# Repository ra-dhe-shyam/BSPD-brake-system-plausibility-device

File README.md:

"# BSPD-brake-system-plausibility-device" 
#BSPD-brake-system-plausibility-device-

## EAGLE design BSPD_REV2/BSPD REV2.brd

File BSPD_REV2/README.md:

Revision 2 of BSPD schematic and layout.

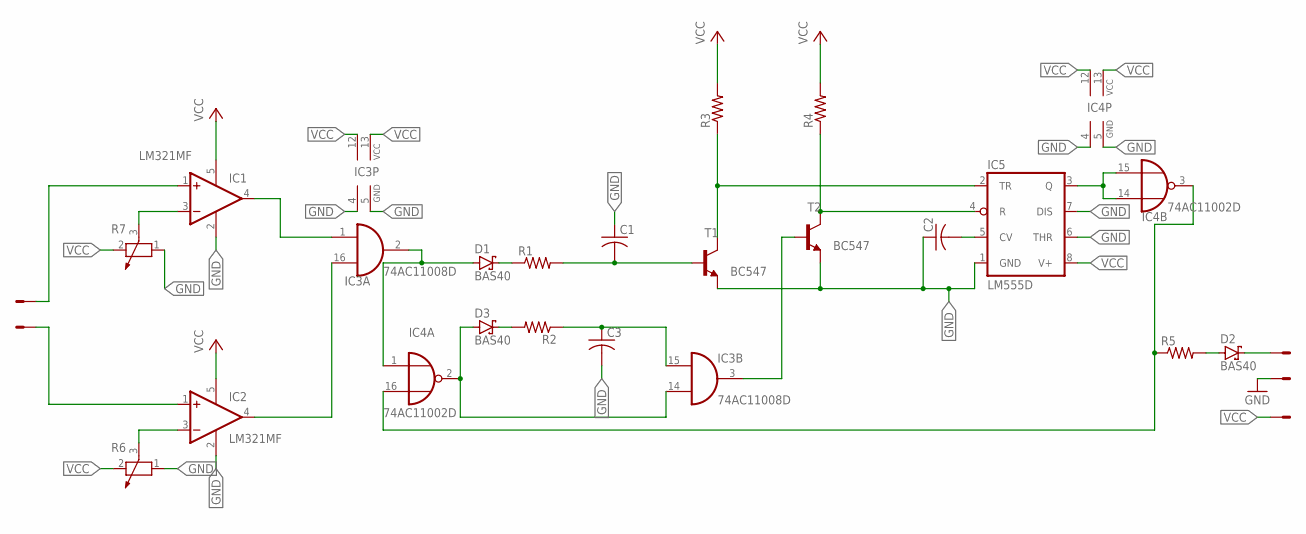
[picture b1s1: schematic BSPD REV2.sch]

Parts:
C1, C2, C3: C-USC0402; C0402
D1, D2, D3: BAS40; SOT23
IC1, IC2: LM321MF; SOT23-5
IC3: 74AC11008D; SO16
IC4: 74AC11002D; SO16
IC5: LM555D; SO08
R1, R2, R3, R4, R5: R-US_M1406; M1406
R6, R7: POTENTIOMETER_PT_SPIN; PT-SPIN
T1, T2: BC547; TO92
X1: 22-23-2051

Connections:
GND: C1.1, C2.1, C3.2, IC1.2 (V-), IC2.2 (V-), IC3.4 (GND), IC3.5 (GND), IC4.4 (GND), IC4.5 (GND), IC5.1 (GND), IC5.6 (THR), IC5.7 (DIS), R6.1, R7.1, T1.1 (E), T2.1 (E), X1.2
unnamed: IC1.1 (+IN), X1.3
unnamed: IC2.1 (+IN), X1.4
unnamed: IC1.3 (-IN), R7.3
unnamed: IC2.3 (-IN), R6.3
unnamed: IC1.4 (OUT), IC3.1 (I0)
unnamed: IC2.4 (OUT), IC3.16 (I1)
unnamed: D1.1 (A), IC3.2 (O), IC4.1 (I0)
unnamed: IC4.3 (O), IC4.16 (I1), R5.1
unnamed: D1.3 (C), R1.1
unnamed: D3.1 (A), IC3.14 (I1), IC4.2 (O)
unnamed: D3.3 (C), R2.2
unnamed: C3.1, IC3.15 (I0), R2.1
unnamed: C1.2, R1.2, T1.2 (B)
unnamed: IC5.2 (TR), R3.1, T1.3 (C)
unnamed: IC5.4 (R), R4.1, T2.3 (C)
unnamed: D2.1 (A), R5.2
unnamed: IC3.3 (O), T2.2 (B)
unnamed: C2.2, IC5.5 (CV)
unnamed: IC4.14 (I1), IC4.15 (I0), IC5.3 (Q)
unnamed: D2.3 (C), X1.1
VCC: IC1.5 (V+), IC2.5 (V+), IC3.12 (VCC), IC3.13 (VCC), IC4.12 (VCC), IC4.13 (VCC), IC5.8 (V+), R3.2, R4.2, R6.2, R7.2, X1.5

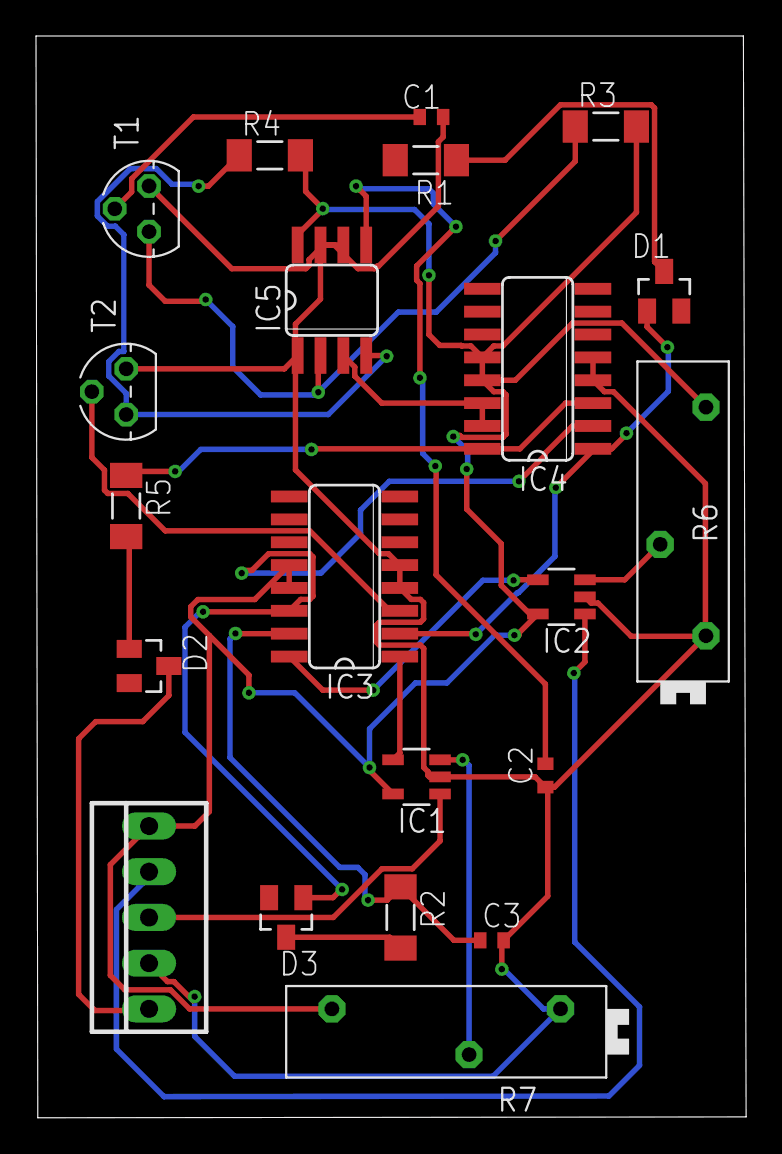
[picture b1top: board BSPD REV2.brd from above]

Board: 2 copper layers, 39.4 x 60.1 mm, 21 parts (0 on the bottom side), 22 nets.

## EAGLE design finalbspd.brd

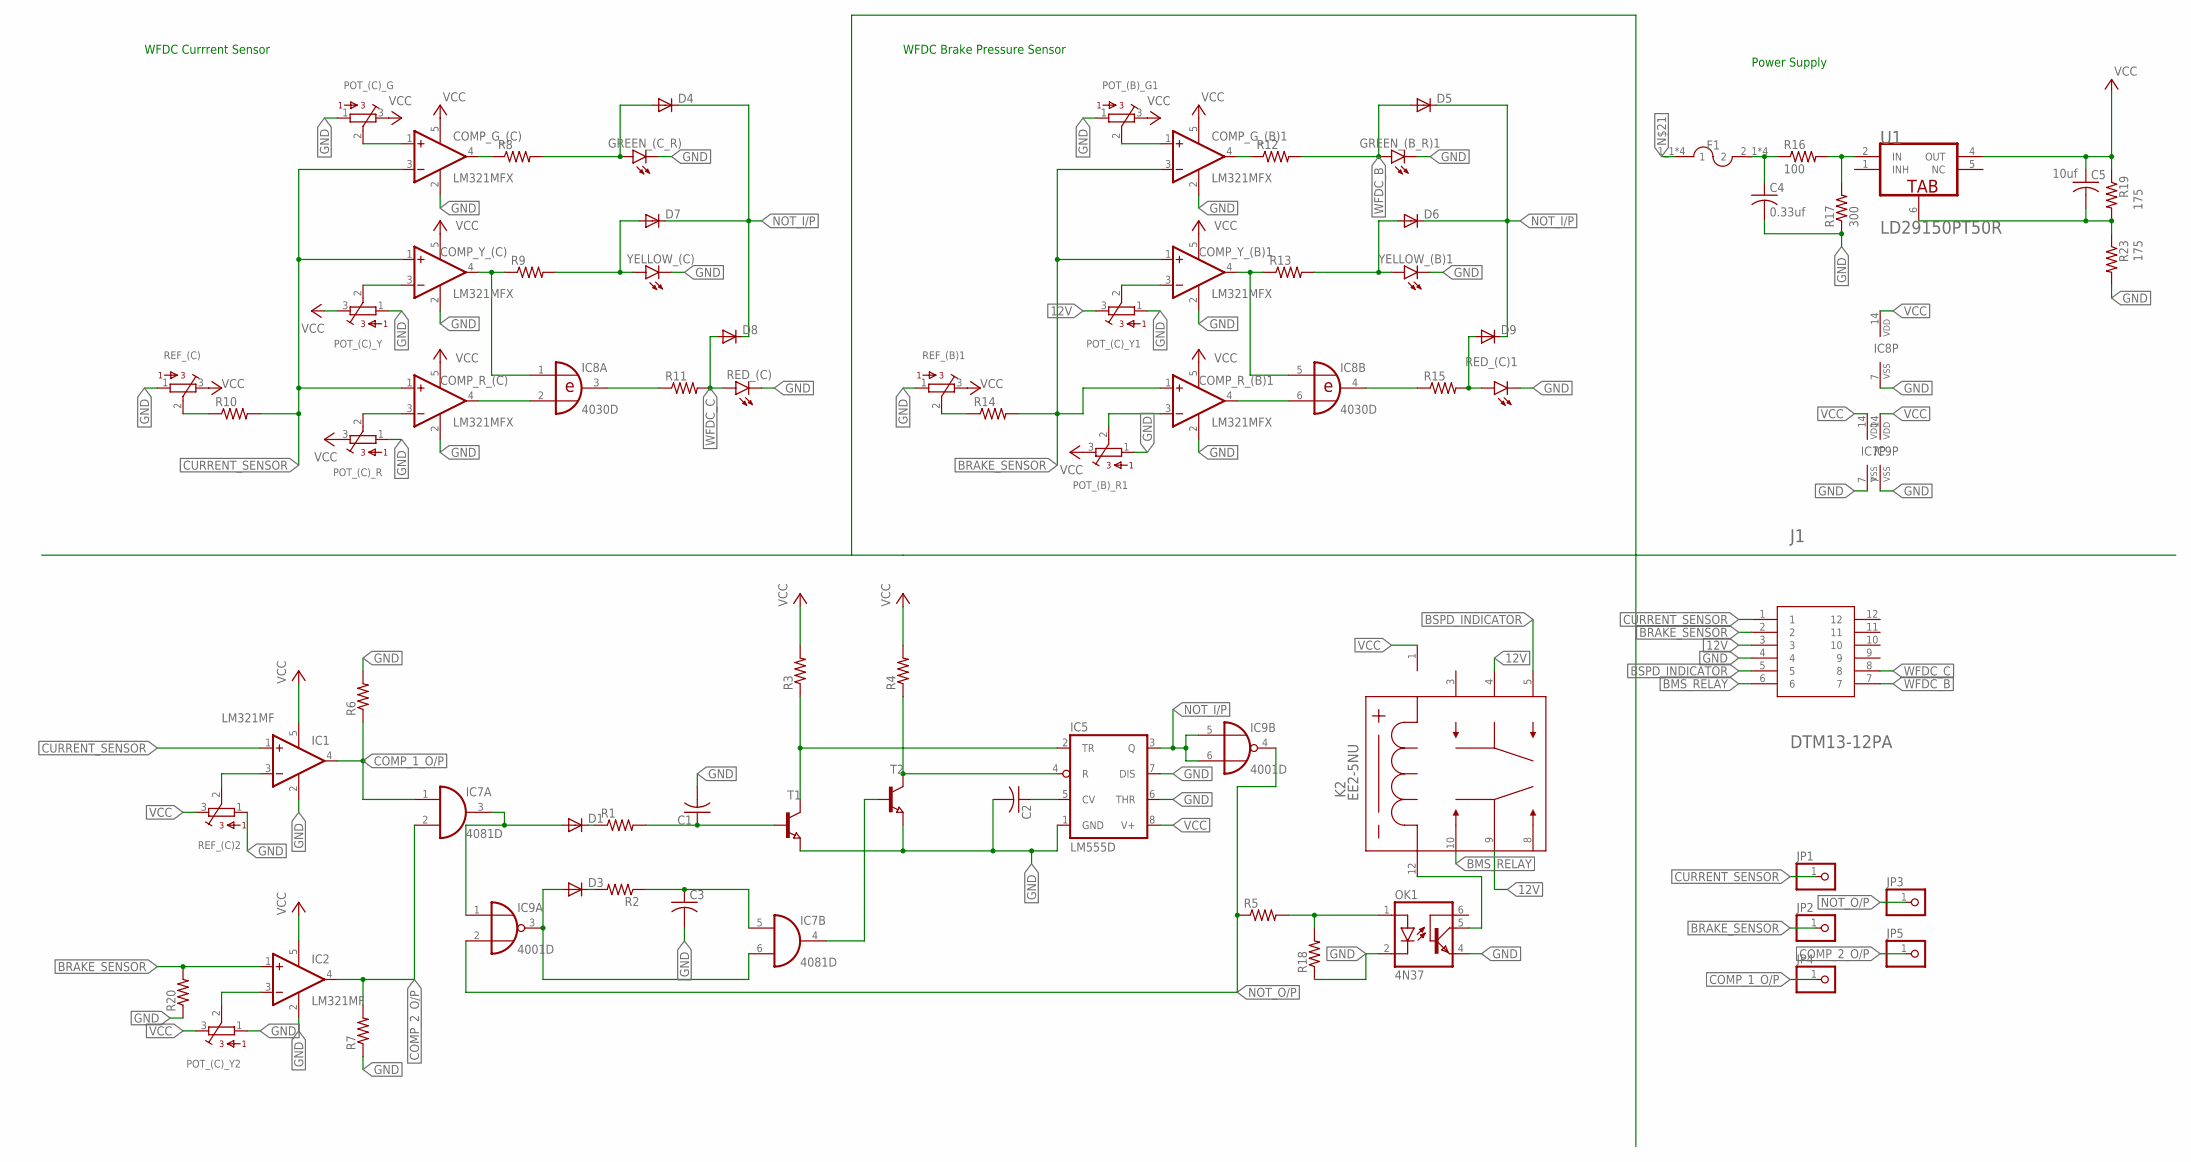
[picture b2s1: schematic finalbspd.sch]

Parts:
C1, C2, C3: C-USC0402; C0402
C4: 0.33uf; C0402
C5: 10uf; C0402
COMP_G_(B)1: LM321MFX; SOT23-5
COMP_G_(C): LM321MFX; SOT23-5
COMP_R_(B)1: LM321MFX; SOT23-5
COMP_R_(C): LM321MFX; SOT23-5
COMP_Y_(B)1: LM321MFX; SOT23-5
COMP_Y_(C): LM321MFX; SOT23-5
D1, D3, D4, D5, D6, D7, D8, D9: DIODE-DO214AC; DO214AC
F1: 178.4265.0002; FUSE_178.4265.0002
GREEN_(B_R)1: GREEN_(C); CHIP-LED0805
GREEN_(C_R): GREEN_(C); CHIP-LED0805
IC1, IC2: LM321MF; SOT23-5
IC5: LM555D; SO08
IC7: 4081D; SO14
IC8: 4030D; SO14
IC9: 4001D; SO14
J1: DTM13-12PA; TE_DTM13-12PA
JP1, JP2, JP3, JP4, JP5: PINHD-1X1; 1X01
K2: EE2-5NU; EE2NU_KEM
OK1: 4N37; DIL06
POT_(B)_G1: 3386-W; 3386W
POT_(B)_R1: 3386-W; 3386W
POT_(C)_G: 3386-W; 3386W
POT_(C)_R: 3386-W; 3386W
POT_(C)_Y, POT_(C)_Y1, POT_(C)_Y2: 3386-W; 3386W
R1, R2, R3, R4, R5, R6, R7, R18, R20: R-US_M1406; M1406
R8, R9, R10, R11, R12, R13, R14, R15: R-US_R1206; R1206
R16: 100; R1206
R17: 300; R1206
R19, R23: 175; R1206
RED_(C), RED_(C)1: LEDCHIP-LED0805; CHIP-LED0805
REF_(B)1: 3386-W; 3386W
REF_(C), REF_(C)2: 3386-W; 3386W
T1, T2: NPN-TRANSISTOR_SOT23; SOT23
U1: STMICROELECTRONICS_LD29150PT50RSTMICROELECTRONICS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; STMICROELECTRONICS_LD29150PT50R_2
YELLOW_(B)1: LEDCHIP-LED0805; CHIP-LED0805
YELLOW_(C): LEDCHIP-LED0805; CHIP-LED0805

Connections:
12V: C4.1, F1.2_1 (2), F1.2_2 (2), F1.2_3 (2), F1.2_4 (2), J1.3, K2.4 (3), K2.9 (6), POT_(C)_Y1.3, R16.1
BMS_RELAY: J1.6, K2.10 (7)
BRAKE_SENSOR: COMP_G_(B)1.3 (-IN), COMP_R_(B)1.1 (+IN), COMP_Y_(B)1.1 (+IN), IC2.1 (+IN), J1.2, JP2.1, R14.2, R20.2
BSPD_INDICATOR: J1.5, K2.5 (4)
COMP_1_O/P: IC1.4 (OUT), IC7.1 (I0), JP4.1, R6.1
COMP_2_O/P: IC2.4 (OUT), IC7.2 (I1), JP5.1, R7.2
CURRENT_SENSOR: COMP_G_(C).3 (-IN), COMP_R_(C).1 (+IN), COMP_Y_(C).1 (+IN), IC1.1 (+IN), J1.1, JP1.1, R10.2
GND: C1.2, C2.2, C3.2, C4.2, COMP_G_(B)1.2 (V-), COMP_G_(C).2 (V-), COMP_R_(B)1.2 (V-), COMP_R_(C).2 (V-), COMP_Y_(B)1.2 (V-), COMP_Y_(C).2 (V-), GREEN_(B_R)1.C, GREEN_(C_R).C, IC1.2 (V-), IC2.2 (V-), IC5.1 (GND), IC5.6 (THR), IC5.7 (DIS), IC7.7 (VSS), IC8.7 (VSS), IC9.7 (VSS), J1.4, OK1.2 (C), OK1.4 (EMI), POT_(B)_G1.1, POT_(B)_R1.1, POT_(C)_G.1, POT_(C)_R.1, POT_(C)_Y.1, POT_(C)_Y1.1, POT_(C)_Y2.1, R6.2, R7.1, R17.1, R18.1, R20.1, R23.2, RED_(C).C, RED_(C)1.C, REF_(B)1.1, REF_(C).1, REF_(C)2.1, T1.2 (E), T2.2 (E), YELLOW_(B)1.C, YELLOW_(C).C
unnamed: C1.1, R1.2, T1.1 (B)
unnamed: IC1.3 (-IN), REF_(C)2.2
unnamed: IC2.3 (-IN), POT_(C)_Y2.2
unnamed: COMP_R_(B)1.3 (-IN), POT_(B)_R1.2
unnamed: K2.12 (8), OK1.5 (COL)
unnamed: D1.A, IC7.3 (O), IC9.1 (I0)
unnamed: C2.1, IC5.5 (CV)
unnamed: D1.C, R1.1
unnamed: D3.A, IC7.6 (I1), IC9.3 (O)
unnamed: D3.C, R2.2
unnamed: C3.1, IC7.5 (I0), R2.1
unnamed: IC5.2 (TR), R3.1, T1.3 (C)
unnamed: IC5.4 (R), R4.1, T2.3 (C)
unnamed: COMP_G_(C).4 (OUT), R8.1
unnamed: OK1.1 (A), R5.2, R18.2
unnamed: IC7.4 (O), T2.1 (B)
unnamed: R16.2, R17.2, U1.2 (IN)
unnamed: F1.1_1 (1), F1.1_2 (1), F1.1_3 (1), F1.1_4 (1)
unnamed: COMP_Y_(C).4 (OUT), IC8.1 (I0), R9.1
unnamed: COMP_R_(C).4 (OUT), IC8.2 (I1)
unnamed: D4.A, GREEN_(C_R).A, R8.2
unnamed: R10.1, REF_(C).2
unnamed: COMP_Y_(C).3 (-IN), POT_(C)_Y.2
unnamed: IC8.3 (O), R11.1
unnamed: COMP_G_(B)1.4 (OUT), R12.1
unnamed: COMP_Y_(B)1.4 (OUT), IC8.5 (I0), R13.1
unnamed: COMP_R_(B)1.4 (OUT), IC8.6 (I1)
unnamed: D9.A, R15.2, RED_(C)1.A
unnamed: D7.A, R9.2, YELLOW_(C).A
unnamed: R14.1, REF_(B)1.2
unnamed: COMP_Y_(B)1.3 (-IN), POT_(C)_Y1.2
unnamed: IC8.4 (O), R15.1
unnamed: D6.A, R13.2, YELLOW_(B)1.A
unnamed: C5.2, R19.2, R23.1, U1.6 (TAB)
NOT_I/P: D4.C, D5.C, D6.C, D7.C, D8.C, D9.C, IC5.3 (Q), IC9.5 (I0), IC9.6 (I1)
NOT_O/P: IC9.2 (I1), IC9.4 (O), JP3.1, R5.1
VCC: C5.1, COMP_G_(B)1.1 (+IN), COMP_G_(B)1.5 (V+), COMP_G_(C).1 (+IN), COMP_G_(C).5 (V+), COMP_R_(B)1.5 (V+), COMP_R_(C).3 (-IN), COMP_R_(C).5 (V+), COMP_Y_(B)1.5 (V+), COMP_Y_(C).5 (V+), IC1.5 (V+), IC2.5 (V+), IC5.8 (V+), IC7.14 (VDD), IC8.14 (VDD), IC9.14 (VDD), K2.1, POT_(B)_G1.2, POT_(B)_G1.3, POT_(B)_R1.3, POT_(C)_G.2, POT_(C)_G.3, POT_(C)_R.2, POT_(C)_R.3, POT_(C)_Y.3, POT_(C)_Y2.3, R3.2, R4.2, R19.1, REF_(B)1.3, REF_(C).3, REF_(C)2.3, U1.4 (OUT)
WFDC_B: D5.A, GREEN_(B_R)1.A, J1.7, R12.2
WFDC_C: D8.A, J1.8, R11.2, RED_(C).A

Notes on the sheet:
WFDC Currrent Sensor
WFDC Brake Pressure Sensor
Power Supply

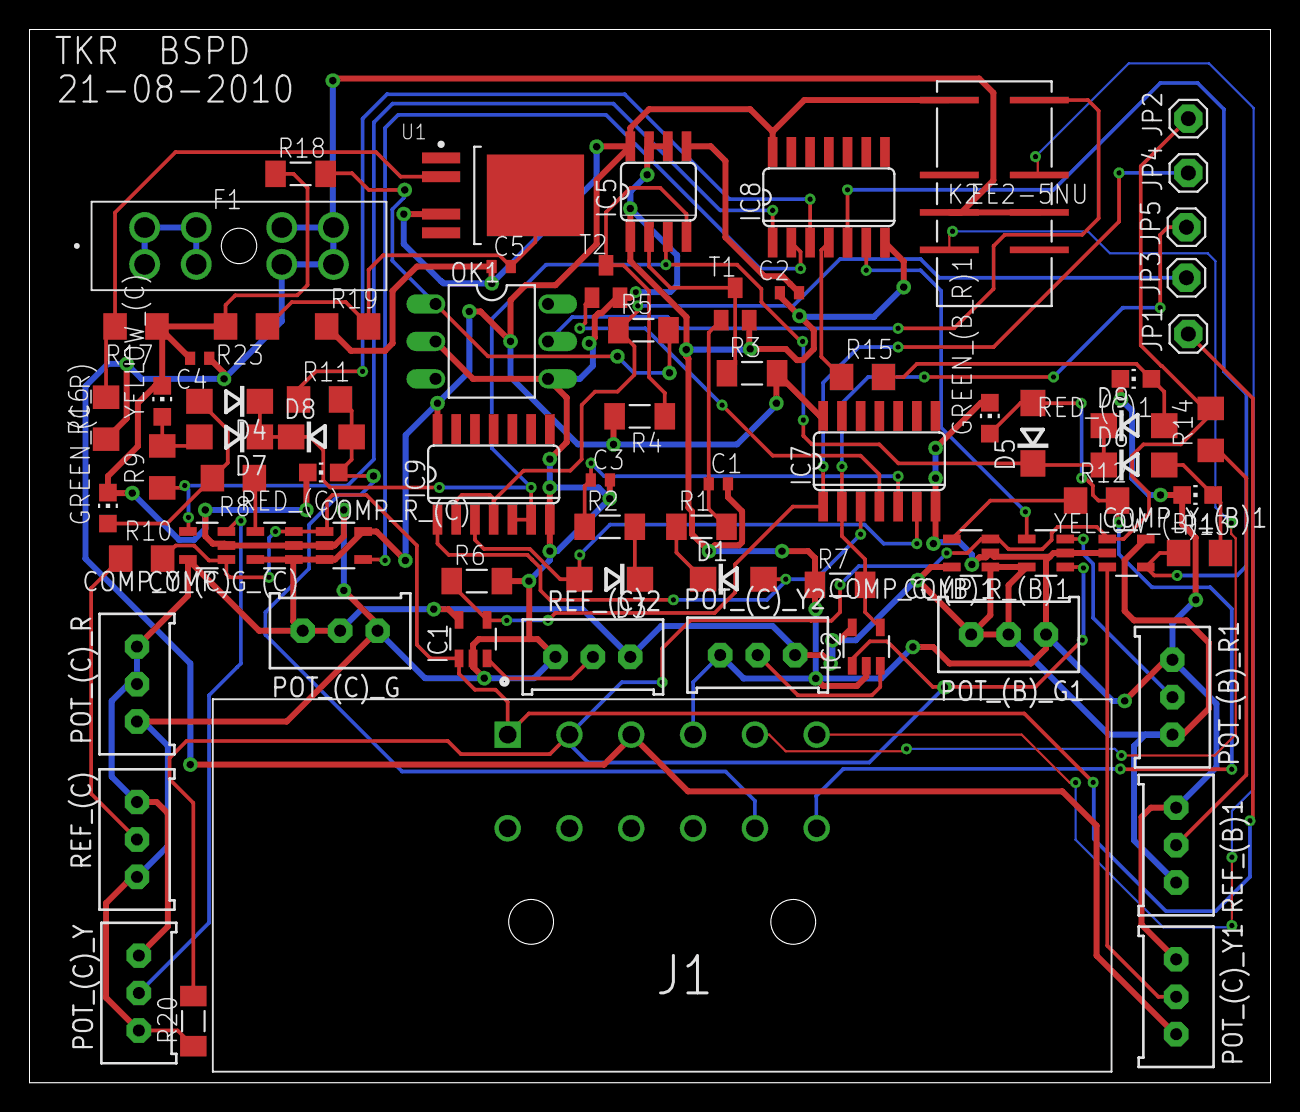
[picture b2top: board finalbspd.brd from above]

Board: 2 copper layers, 84.2 x 71.4 mm, 74 parts (0 on the bottom side), 47 nets.

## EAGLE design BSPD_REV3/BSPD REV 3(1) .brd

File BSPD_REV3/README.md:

Revision 3 of BSPD schematic and layout

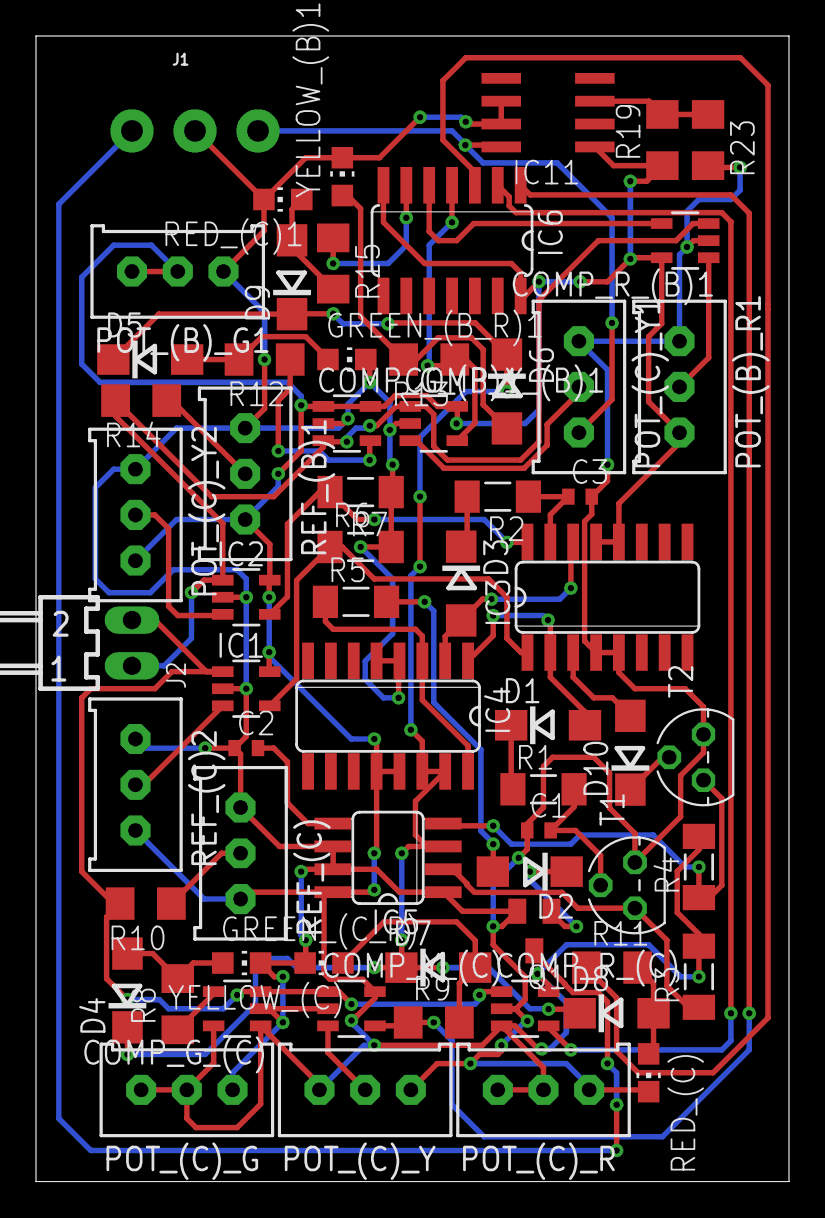
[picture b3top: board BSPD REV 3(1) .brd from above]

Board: 2 copper layers, 41.8 x 63.6 mm, 64 parts (0 on the bottom side), 45 nets.

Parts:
C1, C2, C3: C0402
COMP_G_(B)1: LM321MFX; SOT23-5
COMP_G_(C): LM321MFX; SOT23-5
COMP_R_(B)1: LM321MFX; SOT23-5
COMP_R_(C): LM321MFX; SOT23-5
COMP_Y_(B)1: LM321MFX; SOT23-5
COMP_Y_(C): LM321MFX; SOT23-5
D1, D2, D3, D4, D5, D6, D7, D8, D9, D10: DO214AC
GREEN_(B_R)1: GREEN_(C); CHIP-LED0805
GREEN_(C_R): GREEN_(C); CHIP-LED0805
IC1, IC2: LM321MF; SOT23-5
IC3: 74AC11008D; SO16
IC4: 74AC11002D; SO16
IC5: LM555D; SO08
IC6: 74AC86D; SO14
IC11: SOIC8
J1: SCREWTERMINAL-3.5MM-3-NS
J2: 22-05-7028-02; 7395-02
POT_(B)_G1: 3386W
POT_(B)_R1: 3386W
POT_(C)_G: 3386W
POT_(C)_R: 3386W
POT_(C)_Y, POT_(C)_Y1, POT_(C)_Y2: 3386W
Q1: SOT23
R1, R2, R3, R4, R5, R6, R7: M1406
R8, R9, R10, R11, R12, R13, R14, R15, R19, R23: R1206
RED_(C), RED_(C)1: CHIP-LED0805
REF_(B)1: 3386W
REF_(C), REF_(C)2: 3386W
T1, T2: BC547; TO92
YELLOW_(B)1: CHIP-LED0805
YELLOW_(C): CHIP-LED0805

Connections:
12V: IC11.8, J1.3, POT_(C)_Y1.3
AIR: J1.1, Q1.3
GND: C1.1, C2.1, C3.2, COMP_G_(B)1.2, COMP_G_(C).2, COMP_R_(B)1.2, COMP_R_(C).2, COMP_Y_(B)1.2, COMP_Y_(C).2, GREEN_(B_R)1.C, GREEN_(C_R).C, IC1.2, IC2.2, IC3.4, IC3.5, IC4.4, IC4.5, IC5.1, IC5.6, IC5.7, IC11.6, IC11.7, J1.2, POT_(B)_G1.1, POT_(B)_R1.1, POT_(C)_G.1, POT_(C)_R.1, POT_(C)_Y.1, POT_(C)_Y1.1, POT_(C)_Y2.1, Q1.2, R6.2, R7.1, R23.2, RED_(C).C, RED_(C)1.C, REF_(B)1.1, REF_(C).1, REF_(C)2.1, T1.1, T2.1, YELLOW_(B)1.C, YELLOW_(C).C
unnamed: COMP_R_(B)1.1, POT_(B)_R1.2
unnamed: IC1.3, REF_(C)2.2
unnamed: IC2.3, POT_(C)_Y2.2
unnamed: IC1.4, IC3.1, R6.1
unnamed: IC2.4, IC3.16, R7.2
unnamed: D1.A, IC3.2, IC4.1
unnamed: IC4.3, IC4.16, R5.1
unnamed: D1.C, R1.1
unnamed: D3.A, IC3.14, IC4.2
unnamed: D3.C, R2.2
unnamed: C3.1, IC3.15, R2.1
unnamed: C1.2, R1.2, T1.2
unnamed: IC5.2, R3.1, T1.3
unnamed: IC5.4, R4.1, T2.3
unnamed: COMP_G_(C).4, R8.1
unnamed: D2.A, R5.2
unnamed: D10.A, IC3.3
unnamed: C2.2, IC5.5
unnamed: D2.C, Q1.1
unnamed: COMP_Y_(C).4, IC6.1, R9.1
unnamed: COMP_R_(C).4, IC6.2
unnamed: D4.A, GREEN_(C_R).A, R8.2
unnamed: D8.A, R11.2, RED_(C).A
unnamed: R10.1, REF_(C).2
unnamed: COMP_Y_(C).3, POT_(C)_Y.2
unnamed: IC6.3, R11.1
unnamed: COMP_G_(B)1.4, R12.1
unnamed: COMP_Y_(B)1.4, IC6.4, R13.1
unnamed: COMP_R_(B)1.4, IC6.5
unnamed: D5.A, GREEN_(B_R)1.A, R12.2
unnamed: D9.A, R15.2, RED_(C)1.A
unnamed: D7.A, R9.2, YELLOW_(C).A
unnamed: R14.1, REF_(B)1.2
unnamed: COMP_Y_(B)1.3, POT_(C)_Y1.2
unnamed: IC6.6, R15.1
unnamed: D6.A, R13.2, YELLOW_(B)1.A
unnamed: IC11.3, R19.2, R23.1
unnamed: D10.C, T2.2
NOT_I/P: D4.C, D5.C, D6.C, D7.C, D8.C, D9.C, IC4.14, IC4.15, IC5.3
VCC: COMP_G_(B)1.1, COMP_G_(B)1.5, COMP_G_(C).1, COMP_G_(C).5, COMP_R_(B)1.5, COMP_R_(C).3, COMP_R_(C).5, COMP_Y_(B)1.5, COMP_Y_(C).5, IC1.5, IC2.5, IC3.12, IC3.13, IC4.12, IC4.13, IC5.8, IC6.7, IC6.14, IC11.1, POT_(B)_G1.2, POT_(B)_G1.3, POT_(B)_R1.3, POT_(C)_G.2, POT_(C)_G.3, POT_(C)_R.2, POT_(C)_R.3, POT_(C)_Y.3, POT_(C)_Y2.3, R3.2, R4.2, R19.1, REF_(B)1.3, REF_(C).3, REF_(C)2.3
WFDC_I/P_(B): COMP_G_(B)1.3, COMP_R_(B)1.3, COMP_Y_(B)1.1, IC2.1, J2.1, R14.2
WFDC_I/P_(C): COMP_G_(C).3, COMP_R_(C).1, COMP_Y_(C).1, IC1.1, J2.2, R10.2

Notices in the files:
parts and their libraries:
SparkFun-Connectors: Licensing: Creative Commons ShareAlike 4.0 International - https://creativecommons.org/licenses/by-sa/4.0
